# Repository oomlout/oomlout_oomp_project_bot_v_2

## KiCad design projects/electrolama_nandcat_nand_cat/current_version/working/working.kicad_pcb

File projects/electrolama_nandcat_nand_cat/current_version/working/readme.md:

# nandcat
 
## summary 
* id: electrolama_nandcat_nand_cat
* user: electrolama
* name: nandcat
* board: nand_cat
* repo: https://github.com/electrolama/nandcat
* src_file_repo_kicad_pcb: Revision A/nand-cat.kicad_pcb
* src_file_repo_kicad_pcb_link: https://github.com/electrolama/nandcat/tree/master/Revision A/nand-cat.kicad_pcb

* src_file_repo_sch: Revision A/nand-cat.sch
* src_file_repo_sch_link: https://github.com/electrolama/nandcat/tree/master/Revision A/nand-cat.sch
* full details link: https://github.com/oomlout/oomlout_oomp_project_bot_v_2/tree/main/projects/electrolama_nandcat_nand_cat/current_version/working  

## schematic  
  
[schematic (pdf)](working_schematic.pdf) 

## pcb  

[board (pdf)](working.pdf)  

## working_bom
| Id | Designator | Footprint | Quantity | Designation | Supplier and ref |  | None | 
| --- | --- | --- | --- | --- | --- | --- | --- | 
| 1 | J1 | PinHeader_2x03_P2.54mm_Vertical | 1 | Conn_02x03_Odd_Even |  |  | [''] | 
| 2 | SW2,SW1 | SW_SPST_B3S-1000 | 2 | SW_Push |  |  | [''] | 
| 3 | R2,R4,R1 | R_0603_1608Metric | 3 | 1K |  |  | [''] | 
| 4 | G*** | nand-cat | 1 | LOGO |  |  | [''] | 
| 5 | Q1,Q2 | SOT-23 | 2 | BC847B |  |  | [''] | 
| 6 | R5,R3 | R_0603_1608Metric | 2 | 100K |  |  | [''] | 
| 7 | D1 | LED_D3.0mm | 1 | LED |  |  | [''] | 

## bom_schematic
| Ref | Qnty | Value | Cmp name | Footprint | Description | Vendor | DNP | 
| --- | --- | --- | --- | --- | --- | --- | --- | 
| D1 | 1 | LED | LED | LED_THT:LED_D3.0mm | Light emitting diode |  |  | 
| J1 | 1 | Conn_02x03_Odd_Even | Conn_02x03_Odd_Even | Connector_PinHeader_2.54mm:PinHeader_2x03_P2.54mm_Vertical | Generic connector, double row, 02x03, odd/even pin numbering scheme (row 1 odd numbers, row 2 even numbers), script generated (kicad-library-utils/schlib/autogen/connector/) |  |  | 
| Q1, Q2 | 2 | BC847B | BC847 | Package_TO_SOT_SMD:SOT-23 | 0.1A Ic, 45V Vce, NPN Transistor, SOT-23 |  |  | 
| R1, R2, R4 | 3 | 1K | R | Resistor_SMD:R_0603_1608Metric | Resistor |  |  | 
| R3, R5 | 2 | 100K | R | Resistor_SMD:R_0603_1608Metric | Resistor |  |  | 
| SW1, SW2 | 2 | SW_Push | SW_Push | Button_Switch_SMD:SW_SPST_B3S-1000 | Push button switch, generic, two pins |  |  |

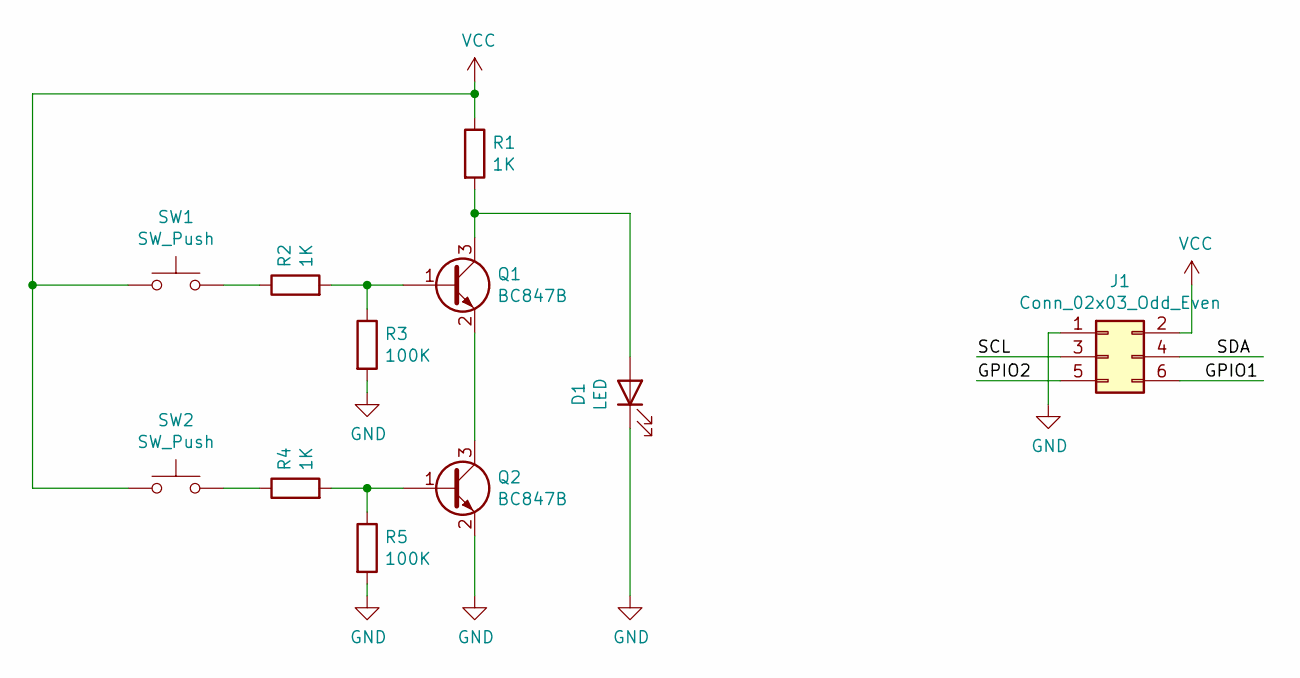
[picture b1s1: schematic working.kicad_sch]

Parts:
D1: LED; LED_D3.0mm
J1: Conn_02x03_Odd_Even; PinHeader_2x03_P2.54mm_Vertical
Q1, Q2: BC847B; SOT-23
R1, R2, R4: 1K; R_0603_1608Metric
R3, R5: 100K; R_0603_1608Metric
SW1, SW2: SW_Push; SW_SPST_B3S-1000

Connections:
/GPIO1: J1.6
/GPIO2: J1.5
/SCL: J1.3
/SDA: J1.4
GND: D1.1 (K), J1.1, Q2.2 (E), R3.2, R5.2
unnamed: D1.2 (A), Q1.3 (C), R1.2
unnamed: Q1.1 (B), R2.2, R3.1
unnamed: Q1.2 (E), Q2.3 (C)
unnamed: Q2.1 (B), R4.2, R5.1
unnamed: R2.1, SW1.2
unnamed: R4.1, SW2.2
VCC: J1.2, R1.1, SW1.1, SW2.1

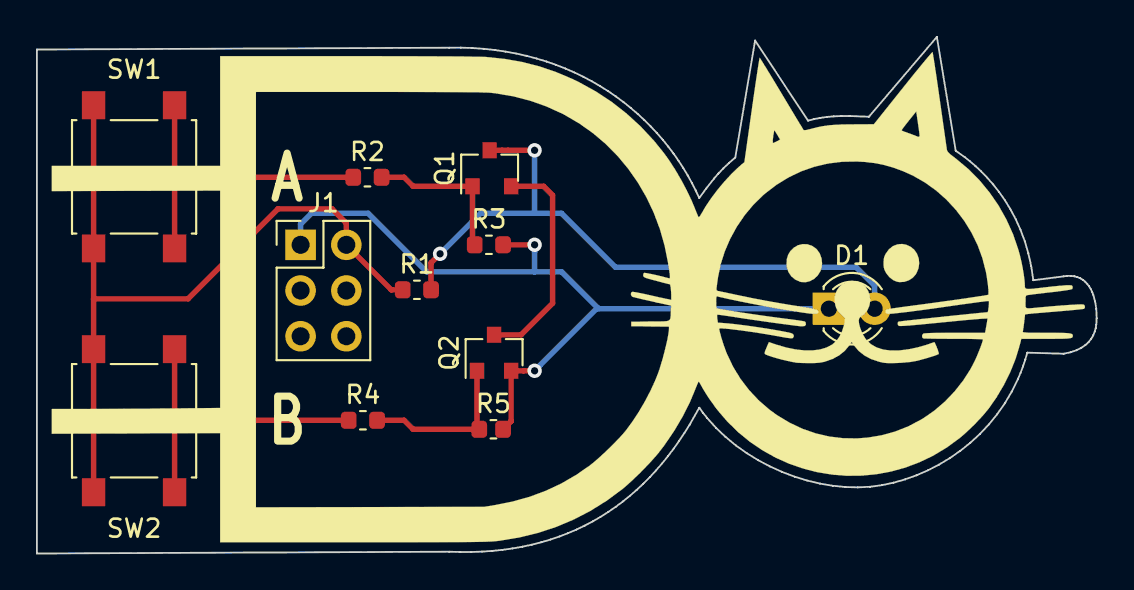
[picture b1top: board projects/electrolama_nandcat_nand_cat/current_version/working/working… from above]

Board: 2 copper layers, 58.9 x 28.7 mm, 11 parts (0 on the bottom side), 8 nets.

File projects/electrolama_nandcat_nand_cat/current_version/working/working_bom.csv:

"Id";"Designator";"Footprint";"Quantity";"Designation";"Supplier and ref";
1;"J1";"PinHeader_2x03_P2.54mm_Vertical";1;"Conn_02x03_Odd_Even";;;
2;"SW2,SW1";"SW_SPST_B3S-1000";2;"SW_Push";;;
3;"R2,R4,R1";"R_0603_1608Metric";3;"1K";;;
4;"G***";"nand-cat";1;"LOGO";;;
5;"Q1,Q2";"SOT-23";2;"BC847B";;;
6;"R5,R3";"R_0603_1608Metric";2;"100K";;;
7;"D1";"LED_D3.0mm";1;"LED";;;

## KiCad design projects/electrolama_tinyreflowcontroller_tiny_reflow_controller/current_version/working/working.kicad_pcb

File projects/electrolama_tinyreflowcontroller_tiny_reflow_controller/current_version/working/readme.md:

# tinyreflowcontroller
 
## summary 
* id: electrolama_tinyreflowcontroller_tiny_reflow_controller
* user: electrolama
* name: tinyreflowcontroller
* board: tiny_reflow_controller
* repo: https://github.com/electrolama/TinyReflowController
* src_file_repo_kicad_pcb: hardware/Revision A1/TINY-REFLOW-CONTROLLER.kicad_pcb
* src_file_repo_kicad_pcb_link: https://github.com/electrolama/TinyReflowController/tree/master/hardware/Revision A1/TINY-REFLOW-CONTROLLER.kicad_pcb
* src_file_repo_kicad_sch: hardware/Revision A1/TINY-REFLOW-CONTROLLER.kicad_sch
* src_file_repo_kicad_sch_link: https://github.com/electrolama/TinyReflowController/tree/master/hardware/Revision A1/TINY-REFLOW-CONTROLLER.kicad_sch

* src_file_repo_sch: 
* src_file_repo_sch_link: https://github.com/electrolama/TinyReflowController/tree/master/
* full details link: https://github.com/oomlout/oomlout_oomp_project_bot_v_2/tree/main/projects/electrolama_tinyreflowcontroller_tiny_reflow_controller/current_version/working  

## schematic  
  
[schematic (pdf)](working_schematic.pdf) 

## pcb  

[board (pdf)](working.pdf)  

## working_bom
| Id | Designator | Footprint | Quantity | Designation | Supplier and ref |  | None | 
| --- | --- | --- | --- | --- | --- | --- | --- | 
| 1 | U3 | TSSOP-14 | 1 | MAX31856 |  |  | [''] | 
| 2 | J2,J1,J5 | TB-1776275-2 | 3 | TERMINAL-BLOCK-1x2 |  |  | [''] | 
| 3 | Q2,Q1,Q3 | SOT-23 | 3 | 2N3904 |  |  | [''] | 
| 4 | R2,R3 | R_0603 | 2 | 100R |  |  | [''] | 
| 5 | R10,R9,R4,R5 | R_0603 | 4 | 10K |  |  | [''] | 
| 6 | R8,R12 | R_0603 | 2 | 53K6 |  |  | [''] | 
| 7 | R7 | R_0603 | 1 | 27K |  |  | [''] | 
| 8 | J3 | MICRO-USB | 1 | MICRO-USB |  |  | [''] | 
| 9 | LOGO1 | LOGO-ROCKET-SCREAM_Without_Text_XXXSmall | 1 | LOGO-ROCKET-SCREAM |  |  | [''] | 
| 10 | L1 | I_0603 | 1 | BLM18KG221SN1D |  |  | [''] | 
| 11 | SW2,SW1 | IT-1102W | 2 | IT-1109S |  |  | [''] | 
| 12 | LS1 | HYG9605B | 1 | HYG9605B |  |  | [''] | 
| 13 | C2,C1 | C_0603 | 2 | 10nF |  |  | [''] | 
| 14 | C9,C8,C7,C6,C4,C3,C13,C14,C18,C17,C11,C19 | C_0603 | 12 | 100nF |  |  | [''] | 
| 15 | C5,C12,C10 | C_0603 | 3 | 10uF 16V X5R |  |  | [''] | 
| 16 | D3 | SOD-323 | 1 | 1N4148WS |  |  | [''] | 
| 17 | R11,R1,R6 | R_0603 | 3 | 2K2 |  |  | [''] | 
| 18 | U1 | QFN-32_5x5mm_Pitch0.5mm | 1 | ATMEGA328P-MU |  |  | [''] | 
| 19 | U4 | MSOP-10 | 1 | CH340E |  |  | [''] | 
| 20 | F1 | MF-FSMF | 1 | FUSE |  |  | [''] | 
| 21 | L2 | I_0603 | 1 | LBMF1608T100K |  |  | [''] | 
| 22 | C16,C15 | C_0603 | 2 | 10pF |  |  | [''] | 
| 23 | D1 | LED_0603 | 1 | Red |  |  | [''] | 
| 24 | U2 | SOT-23 | 1 | MCP1700T-3302E-TT |  |  | [''] | 
| 25 | J9,J7,J8,J6 | PinHeader_1x02_P2.54mm_Vertical | 4 | 1x2 |  |  | [''] | 
| 26 | Y1 | Crystal_SMD_5032-2Pin_5.0x3.2mm | 1 | NX3225GD |  |  | [''] | 
| 27 | H1,H2,H4,H3 | MountingHole_2.2mm_M2 | 4 | M2 |  |  | [''] | 
| 28 | J10 | PinHeader_1x04_P2.54mm_Vertical | 1 | Conn_01x04 |  |  | [''] | 
| 29 | J4 | HDR_2x3_Pitch2.54mm | 1 | 2.54mm 2x3 |  |  | [''] | 
| 30 | LOGO2 | LOGO-KICAD_XSmall | 1 | LOGO-KICAD |  |  | [''] | 
| 31 | LOGO3 | LOGO-ROCKET-SCREAM_Vertical_Small | 1 | LOGO-ROCKET-SCREAM |  |  | [''] | 

## bom_schematic
| Ref | Qnty | Value | Cmp name | Footprint | Description | Vendor | DNP | 
| --- | --- | --- | --- | --- | --- | --- | --- | 
| C1, C2 | 2 | 10nF | CAPACITOR-CERAMIC-RocketScreamKiCadLib | RocketScreamKiCadLib:C_0603 |  |  |  | 
| C3, C4, C6, C7, C8, C9, C11, C13, C14, C17, C18, C19 | 12 | 100nF | CAPACITOR-CERAMIC-RocketScreamKiCadLib | RocketScreamKiCadLib:C_0603 |  |  |  | 
| C5, C10, C12 | 3 | 10uF 16V X5R | CAPACITOR-CERAMIC-RocketScreamKiCadLib | RocketScreamKiCadLib:C_0603 |  |  |  | 
| C15, C16 | 2 | 10pF | CAPACITOR-CERAMIC-RocketScreamKiCadLib | RocketScreamKiCadLib:C_0603 |  |  |  | 
| D1 | 1 | Red | LED-SINGLE-RocketScreamKiCadLib | RocketScreamKiCadLib:LED_0603 |  |  |  | 
| D3 | 1 | 1N4148WS | DIODE-RocketScreamKiCadLib | RocketScreamKiCadLib:SOD-323 |  |  |  | 
| F1 | 1 | FUSE | FUSE-RocketScreamKiCadLib | RocketScreamKiCadLib:MF-FSMF |  |  |  | 
| H1, H2, H3, H4 | 4 | M2 | MountingHole | MountingHole:MountingHole_2.2mm_M2 | Mounting Hole without connection |  |  | 
| J1, J2, J5 | 3 | TERMINAL-BLOCK-1x2 | TERMINAL-BLOCK-1x2-RocketScreamKiCadLib | RocketScreamKiCadLib:TB-1776275-2 |  |  |  | 
| J3 | 1 | MICRO-USB | MICRO-USB-RocketScreamKiCadLib | RocketScreamKiCadLib:MICRO-USB |  |  |  | 
| J4 | 1 | 2.54mm 2x3 | CONN-HDR-2x3-RocketScreamKiCadLib | RocketScreamKiCadLib:HDR_2x3_Pitch2.54mm |  |  |  | 
| J6, J7, J8, J9 | 4 | 1x2 | Conn_01x02 | Connector_PinHeader_2.54mm:PinHeader_1x02_P2.54mm_Vertical | Generic connector, single row, 01x02, script generated (kicad-library-utils/schlib/autogen/connector/) |  |  | 
| J10 | 1 | Conn_01x04 | Conn_01x04 | Connector_PinHeader_2.54mm:PinHeader_1x04_P2.54mm_Vertical | Generic connector, single row, 01x04, script generated (kicad-library-utils/schlib/autogen/connector/) |  |  | 
| L1 | 1 | BLM18KG221SN1D | INDUCTOR-RocketScreamKiCadLib | RocketScreamKiCadLib:I_0603 |  |  |  | 
| L2 | 1 | LBMF1608T100K | INDUCTOR-RocketScreamKiCadLib | RocketScreamKiCadLib:I_0603 |  |  |  | 
| LOGO1 | 1 | LOGO-ROCKET-SCREAM | LOGO-ROCKET-SCREAM-WITHOUT-TEXT-RocketScreamKiCadLib | RocketScreamKiCadLib:LOGO-ROCKET-SCREAM_Without_Text_XXXSmall |  |  |  | 
| LOGO2 | 1 | LOGO-KICAD | LOGO-KICAD-RocketScreamKiCadLib | RocketScreamKiCadLib:LOGO-KICAD_XSmall |  |  |  | 
| LOGO3 | 1 | LOGO-ROCKET-SCREAM | LOGO-ROCKET-SCREAM-WITHOUT-TEXT-RocketScreamKiCadLib | RocketScreamKiCadLib:LOGO-ROCKET-SCREAM_Vertical_Small |  |  |  | 
| LS1 | 1 | HYG9605B | BUZZER-RocketScreamKiCadLib | RocketScreamKiCadLib:HYG9605B |  |  |  | 
| Q1, Q2, Q3 | 3 | 2N3904 | BJT-NPN-RocketScreamKiCadLib | RocketScreamKiCadLib:SOT-23 |  |  |  | 
| R1, R6, R11 | 3 | 2K2 | RESISTOR-RocketScreamKiCadLib | RocketScreamKiCadLib:R_0603 |  |  |  | 
| R2, R3 | 2 | 100R | RESISTOR-RocketScreamKiCadLib | RocketScreamKiCadLib:R_0603 |  |  |  | 
| R4, R5, R9, R10 | 4 | 10K | RESISTOR-RocketScreamKiCadLib | RocketScreamKiCadLib:R_0603 |  |  |  | 
| R7 | 1 | 27K | RESISTOR-RocketScreamKiCadLib | RocketScreamKiCadLib:R_0603 |  |  |  | 
| R8, R12 | 2 | 53K6 | RESISTOR-RocketScreamKiCadLib | RocketScreamKiCadLib:R_0603 |  |  |  | 
| SW1, SW2 | 2 | IT-1109S | TACT-SWITCH_4Pins-RocketScreamKiCadLib | RocketScreamKiCadLib:IT-1102W |  |  |  | 
| U1 | 1 | ATMEGA328P-MU | ATMEGA328P-MU-RocketScreamKiCadLib | RocketScreamKiCadLib:QFN-32_5x5mm_Pitch0.5mm |  |  |  | 
| U2 | 1 | MCP1700T-3302E-TT | MCP1700T-XXX2E-TT-RocketScreamKiCadLib | RocketScreamKiCadLib:SOT-23 |  |  |  | 
| U3 | 1 | MAX31856 | MAX31856-RocketScreamKiCadLib | RocketScreamKiCadLib:TSSOP-14 |  |  |  | 
| U4 | 1 | CH340E | CH340E-RocketScreamKiCadLib | RocketScreamKiCadLib:MSOP-10 |  |  |  | 
| Y1 | 1 | NX3225GD | CRYSTAL-RocketScreamKiCadLib | Crystal:Crystal_SMD_5032-2Pin_5.0x3.2mm |  |  |  |

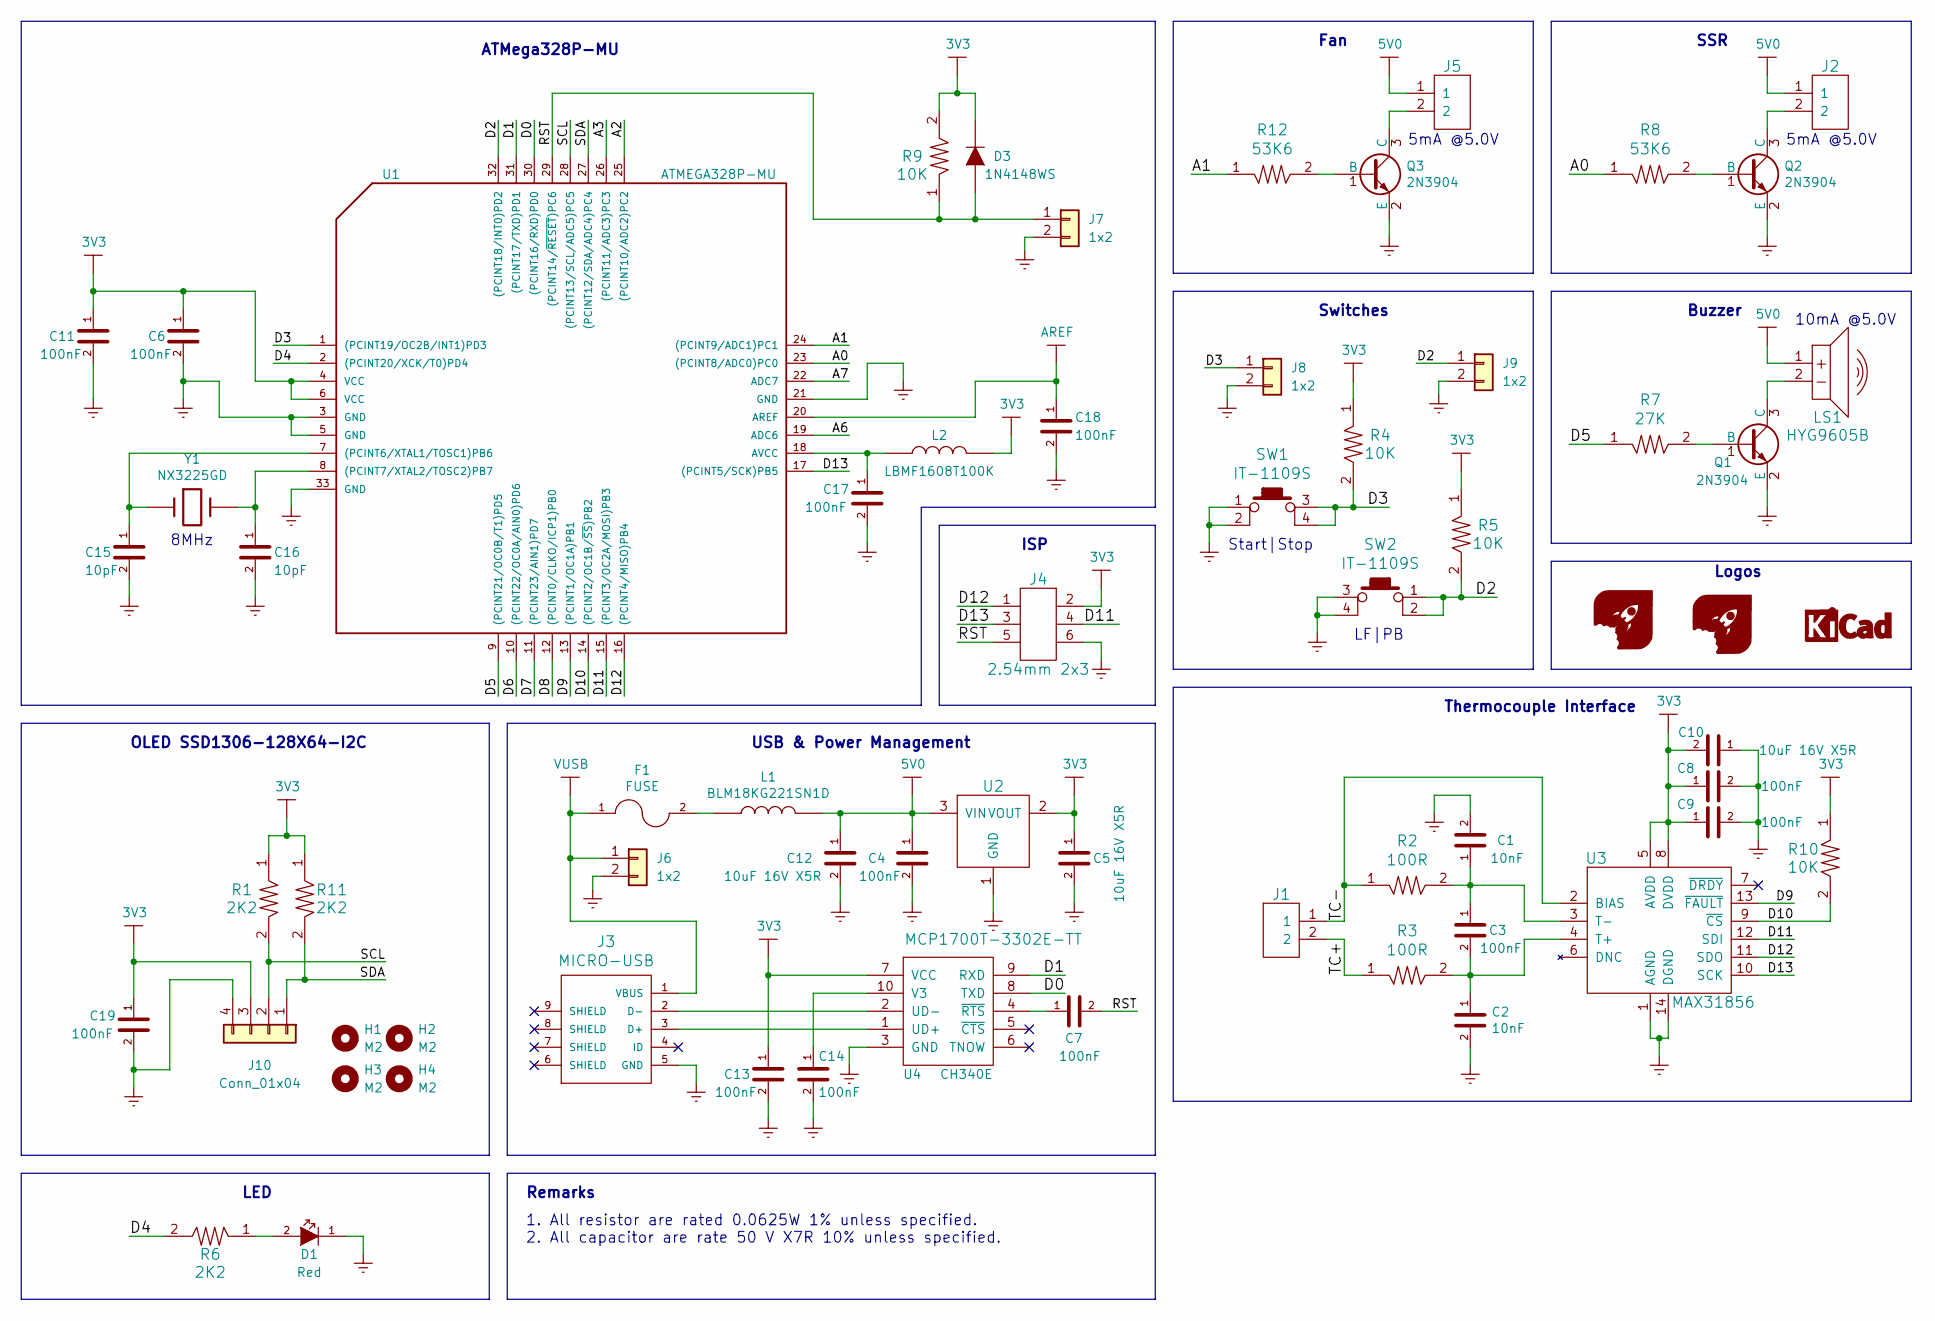
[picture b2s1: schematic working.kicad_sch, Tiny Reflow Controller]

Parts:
C1, C2: 10nF; C_0603
C3, C4, C6, C7, C8, C9, C11, C13, C14, C17, C18, C19: 100nF; C_0603
C5, C10, C12: 10uF 16V X5R; C_0603
C15, C16: 10pF; C_0603
D1: Red; LED_0603
D3: 1N4148WS; SOD-323
F1: FUSE; MF-FSMF
H1, H2, H3, H4: M2; MountingHole_2.2mm_M2
J1, J2, J5: TERMINAL-BLOCK-1x2; TB-1776275-2
J3: MICRO-USB
J4: 2.54mm 2x3; HDR_2x3_Pitch2.54mm
J6, J7, J8, J9: 1x2; PinHeader_1x02_P2.54mm_Vertical
J10: Conn_01x04; PinHeader_1x04_P2.54mm_Vertical
L1: BLM18KG221SN1D; I_0603
L2: LBMF1608T100K; I_0603
LOGO1: LOGO-ROCKET-SCREAM; LOGO-ROCKET-SCREAM_Without_Text_XXXSmall
LOGO2: LOGO-KICAD; LOGO-KICAD_XSmall
LOGO3: LOGO-ROCKET-SCREAM; LOGO-ROCKET-SCREAM_Vertical_Small
LS1: HYG9605B
Q1, Q2, Q3: 2N3904; SOT-23
R1, R6, R11: 2K2; R_0603
R2, R3: 100R; R_0603
R4, R5, R9, R10: 10K; R_0603
R7: 27K; R_0603
R8, R12: 53K6; R_0603
SW1, SW2: IT-1109S; IT-1102W
U1: ATMEGA328P-MU; QFN-32_5x5mm_Pitch0.5mm
U2: MCP1700T-3302E-TT; SOT-23
U3: MAX31856; TSSOP-14
U4: CH340E; MSOP-10
Y1: NX3225GD; Crystal_SMD_5032-2Pin_5.0x3.2mm

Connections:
3V3: C5.1, C6.1, C8.1, C9.1, C10.2, C11.1, C13.1, C19.1, D3.1 (K), J4.2, J10.3, L2.2, R1.1, R4.1, R5.1, R9.2, R10.1, R11.1, U1.4 (VCC), U1.6 (VCC), U2.2 (VOUT), U3.5 (AVDD), U3.8 (DVDD), U4.7 (VCC)
5V0: C4.1, C12.1, J2.1, J5.1, L1.2, LS1.1, U2.3 (VIN)
/A0: R8.1, U1.23 ((PCINT8/ADC0)PC0)
/A1: R12.1, U1.24 ((PCINT9/ADC1)PC1)
/A2: U1.25 ((PCINT10/ADC2)PC2)
/A3: U1.26 ((PCINT11/ADC3)PC3)
/A6: U1.19 (ADC6)
/A7: U1.22 (ADC7)
/D0: U1.30 ((PCINT16/RXD)PD0), U4.8 (TXD)
/D1: U1.31 ((PCINT17/TXD)PD1), U4.9 (RXD)
/D2: J9.1, R5.2, SW2.1, SW2.2, U1.32 ((PCINT18/INT0)PD2)
/D3: J8.1, R4.2, SW1.3, SW1.4, U1.1 ((PCINT19/OC2B/INT1)PD3)
/D4: R6.2, U1.2 ((PCINT20/XCK/T0)PD4)
/D5: R7.1, U1.9 ((PCINT21/OC0B/T1)PD5)
/D6: U1.10 ((PCINT22/OC0A/AIN0)PD6)
/D7: U1.11 ((PCINT23/AIN1)PD7)
/D8: U1.12 ((PCINT0/CLKO/ICP1)PB0)
/D9: U1.13 ((PCINT1/OC1A)PB1), U3.13 (~FAULT)
/D10: R10.2, U1.14 ((PCINT2/OC1B/~SS)PB2), U3.9 (~CS)
/D11: J4.4, U1.15 ((PCINT3/OC2A/MOSI)PB3), U3.12 (SDI)
/D12: J4.1, U1.16 ((PCINT4/MISO)PB4), U3.11 (SDO)
/D13: J4.3, U1.17 ((PCINT5/SCK)PB5), U3.10 (SCK)
/RST: C7.2, D3.2 (A), J4.5, J7.1, R9.1, U1.29 ((PCINT14/~RESET)PC6)
/SCL: J10.2, R1.2, U1.28 ((PCINT13/SCL/ADC5)PC5)
/SDA: J10.1, R11.2, U1.27 ((PCINT12/SDA/ADC4)PC4)
/TC+: J1.2, R3.1
/TC-: J1.1, R2.1, U3.2 (BIAS)
AREF: C18.1, U1.20 (AREF)
GND: C1.2, C2.2, C4.2, C5.2, C6.2, C8.2, C9.2, C10.1, C11.2, C12.2, C13.2, C14.2, C15.2, C16.2, C17.2, C18.2, C19.2, D1.1 (K), J3.5 (GND), J4.6, J6.2, J7.2, J8.2, J9.2, J10.4, Q1.2 (E), Q2.2 (E), Q3.2 (E), SW1.1, SW1.2, SW2.3, SW2.4, U1.3 (GND), U1.5 (GND), U1.21 (GND), U1.33 (GND), U2.1 (GND), U3.1 (AGND), U3.14 (DGND), U4.3 (GND)
unnamed: C1.1, C3.1, R2.2, U3.3 (T-)
unnamed: C2.1, C3.2, R3.2, U3.4 (T+)
unnamed: C7.1, U4.4 (~RTS)
unnamed: C14.1, U4.10 (V3)
unnamed: C15.1, U1.7 ((PCINT6/XTAL1/TOSC1)PB6), Y1.1
unnamed: C16.1, U1.8 ((PCINT7/XTAL2/TOSC2)PB7), Y1.2
unnamed: C17.1, L2.1, U1.18 (AVCC)
unnamed: D1.2 (A), R6.1
unnamed: F1.2, L1.1
unnamed: J2.2, Q2.3 (C)
unnamed: J3.2 (D-), U4.2 (UD-)
unnamed: J3.3 (D+), U4.1 (UD+)
unnamed: J5.2, Q3.3 (C)
unnamed: LS1.2, Q1.3 (C)
unnamed: Q1.1 (B), R7.2
unnamed: Q2.1 (B), R8.2
unnamed: Q3.1 (B), R12.2
VUSB: F1.1, J3.1 (VBUS), J6.1

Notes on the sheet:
Buzzer
5mA @5.0V
Fan
Logos
LF|PB
Remarks
10mA @5.0V
Switches
Start|Stop
1. All resistor are rated 0.0625W 1% unless specified. 2. All capacitor are rate 50 V X7R 10% unless specified.
ISP
Thermocouple Interface
8MHz
LED
ATMega328P-MU
USB & Power Management
SSR
OLED SSD1306-128X64-I2C

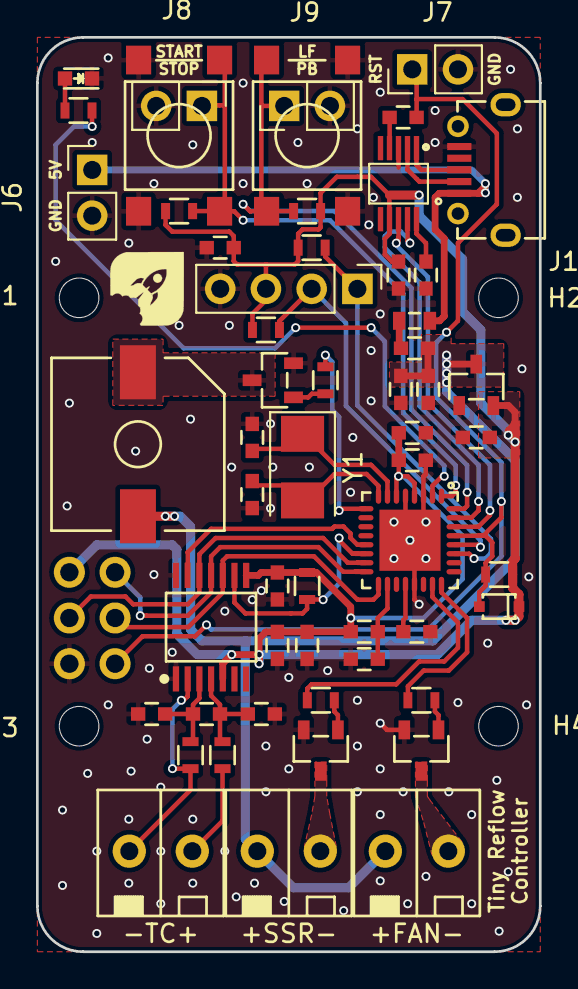
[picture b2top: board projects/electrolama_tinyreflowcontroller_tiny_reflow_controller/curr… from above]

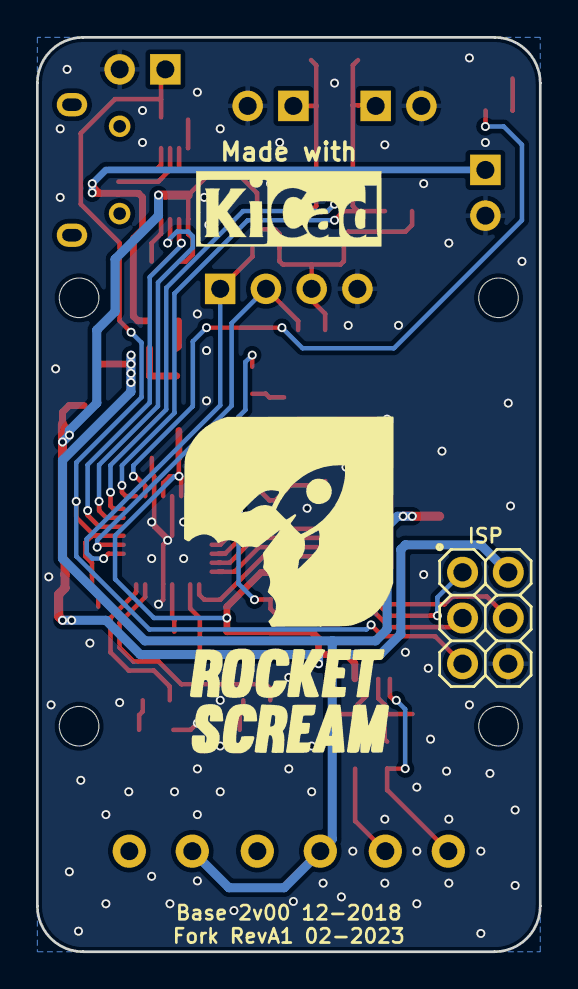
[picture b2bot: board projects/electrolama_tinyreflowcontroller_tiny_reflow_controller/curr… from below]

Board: 2 copper layers, 27.9 x 50.8 mm, 64 parts (3 on the bottom side), 40 nets.

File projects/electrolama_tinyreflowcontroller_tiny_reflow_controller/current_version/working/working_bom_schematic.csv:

"Source:","C:\gh\oomlout_oomp_project_bot_v_2\projects\electrolama_tinyreflowcontroller_tiny_reflow_controller\current_version\working\working.kicad_sch"
"Date:","11/09/2023 23:51:04"
"Tool:","Eeschema 7.0.6"
"Generator:","C:/Program Files/KiCad/7.0/bin/scripting/plugins/bom_csv_grouped_by_value_with_fp.py"
"Component Count:","64"
"Ref","Qnty","Value","Cmp name","Footprint","Description","Vendor","DNP"
"C1, C2","2","10nF","CAPACITOR-CERAMIC-RocketScreamKiCadLib","RocketScreamKiCadLib:C_0603","","",""
"C3, C4, C6, C7, C8, C9, C11, C13, C14, C17, C18, C19","12","100nF","CAPACITOR-CERAMIC-RocketScreamKiCadLib","RocketScreamKiCadLib:C_0603","","",""
"C5, C10, C12","3","10uF 16V X5R","CAPACITOR-CERAMIC-RocketScreamKiCadLib","RocketScreamKiCadLib:C_0603","","",""
"C15, C16","2","10pF","CAPACITOR-CERAMIC-RocketScreamKiCadLib","RocketScreamKiCadLib:C_0603","","",""
"D1","1","Red","LED-SINGLE-RocketScreamKiCadLib","RocketScreamKiCadLib:LED_0603","","",""
"D3","1","1N4148WS","DIODE-RocketScreamKiCadLib","RocketScreamKiCadLib:SOD-323","","",""
"F1","1","FUSE","FUSE-RocketScreamKiCadLib","RocketScreamKiCadLib:MF-FSMF","","",""
"H1, H2, H3, H4","4","M2","MountingHole","MountingHole:MountingHole_2.2mm_M2","Mounting Hole without connection","",""
"J1, J2, J5","3","TERMINAL-BLOCK-1x2","TERMINAL-BLOCK-1x2-RocketScreamKiCadLib","RocketScreamKiCadLib:TB-1776275-2","","",""
"J3","1","MICRO-USB","MICRO-USB-RocketScreamKiCadLib","RocketScreamKiCadLib:MICRO-USB","","",""
"J4","1","2.54mm 2x3","CONN-HDR-2x3-RocketScreamKiCadLib","RocketScreamKiCadLib:HDR_2x3_Pitch2.54mm","","",""
"J6, J7, J8, J9","4","1x2","Conn_01x02","Connector_PinHeader_2.54mm:PinHeader_1x02_P2.54mm_Vertical","Generic connector, single row, 01x02, script generated (kicad-library-utils/schlib/autogen/connector/)","",""
"J10","1","Conn_01x04","Conn_01x04","Connector_PinHeader_2.54mm:PinHeader_1x04_P2.54mm_Vertical","Generic connector, single row, 01x04, script generated (kicad-library-utils/schlib/autogen/connector/)","",""
"L1","1","BLM18KG221SN1D","INDUCTOR-RocketScreamKiCadLib","RocketScreamKiCadLib:I_0603","","",""
"L2","1","LBMF1608T100K","INDUCTOR-RocketScreamKiCadLib","RocketScreamKiCadLib:I_0603","","",""
"LOGO1","1","LOGO-ROCKET-SCREAM","LOGO-ROCKET-SCREAM-WITHOUT-TEXT-RocketScreamKiCadLib","RocketScreamKiCadLib:LOGO-ROCKET-SCREAM_Without_Text_XXXSmall","","",""
"LOGO2","1","LOGO-KICAD","LOGO-KICAD-RocketScreamKiCadLib","RocketScreamKiCadLib:LOGO-KICAD_XSmall","","",""
"LOGO3","1","LOGO-ROCKET-SCREAM","LOGO-ROCKET-SCREAM-WITHOUT-TEXT-RocketScreamKiCadLib","RocketScreamKiCadLib:LOGO-ROCKET-SCREAM_Vertical_Small","","",""
"LS1","1","HYG9605B","BUZZER-RocketScreamKiCadLib","RocketScreamKiCadLib:HYG9605B","","",""
"Q1, Q2, Q3","3","2N3904","BJT-NPN-RocketScreamKiCadLib","RocketScreamKiCadLib:SOT-23","","",""
"R1, R6, R11","3","2K2","RESISTOR-RocketScreamKiCadLib","RocketScreamKiCadLib:R_0603","","",""
"R2, R3","2","100R","RESISTOR-RocketScreamKiCadLib","RocketScreamKiCadLib:R_0603","","",""
"R4, R5, R9, R10","4","10K","RESISTOR-RocketScreamKiCadLib","RocketScreamKiCadLib:R_0603","","",""
"R7","1","27K","RESISTOR-RocketScreamKiCadLib","RocketScreamKiCadLib:R_0603","","",""
"R8, R12","2","53K6","RESISTOR-RocketScreamKiCadLib","RocketScreamKiCadLib:R_0603","","",""
"SW1, SW2","2","IT-1109S","TACT-SWITCH_4Pins-RocketScreamKiCadLib","RocketScreamKiCadLib:IT-1102W","","",""
"U1","1","ATMEGA328P-MU","ATMEGA328P-MU-RocketScreamKiCadLib","RocketScreamKiCadLib:QFN-32_5x5mm_Pitch0.5mm","","",""
"U2","1","MCP1700T-3302E-TT","MCP1700T-XXX2E-TT-RocketScreamKiCadLib","RocketScreamKiCadLib:SOT-23","","",""
"U3","1","MAX31856","MAX31856-RocketScreamKiCadLib","RocketScreamKiCadLib:TSSOP-14","","",""
"U4","1","CH340E","CH340E-RocketScreamKiCadLib","RocketScreamKiCadLib:MSOP-10","","",""
"Y1","1","NX3225GD","CRYSTAL-RocketScreamKiCadLib","Crystal:Crystal_SMD_5032-2Pin_5.0x3.2mm","","",""

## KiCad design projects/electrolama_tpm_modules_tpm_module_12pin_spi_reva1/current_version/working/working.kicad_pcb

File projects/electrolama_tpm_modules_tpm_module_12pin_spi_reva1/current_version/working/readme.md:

# tpm_modules
 
## summary 
* id: electrolama_tpm_modules_tpm_module_12pin_spi_reva1
* user: electrolama
* name: tpm_modules
* board: tpm_module_12pin_spi_reva1
* repo: https://github.com/electrolama/tpm-modules
* src_file_repo_kicad_pcb: tpm-module-12pin-spi/Revision A1/tpm-module-12pin-spi-RevA1.kicad_pcb
* src_file_repo_kicad_pcb_link: https://github.com/electrolama/tpm-modules/tree/main/tpm-module-12pin-spi/Revision A1/tpm-module-12pin-spi-RevA1.kicad_pcb
* src_file_repo_kicad_sch: tpm-module-12pin-spi/Revision A1/tpm-module-12pin-spi-RevA1.kicad_sch
* src_file_repo_kicad_sch_link: https://github.com/electrolama/tpm-modules/tree/main/tpm-module-12pin-spi/Revision A1/tpm-module-12pin-spi-RevA1.kicad_sch

* src_file_repo_sch: 
* src_file_repo_sch_link: https://github.com/electrolama/tpm-modules/tree/main/
* full details link: https://github.com/oomlout/oomlout_oomp_project_bot_v_2/tree/main/projects/electrolama_tpm_modules_tpm_module_12pin_spi_reva1/current_version/working  

## schematic  
  
[schematic (pdf)](working_schematic.pdf) 

## pcb  

[board (pdf)](working.pdf)  

## working_bom
| Id | Designator | Footprint | Quantity | Designation | Supplier and ref |  | None | 
| --- | --- | --- | --- | --- | --- | --- | --- | 
| 1 | C2,C3 | C_0402_1005Metric | 2 | 100n |  |  | [''] | 
| 2 | IC1 | QFN-32-1EP_5x5mm_P0.5mm_EP3.1x3.1mm | 1 | Infineon-SLB9670 |  |  | [''] | 
| 3 | C1 | C_0402_1005Metric | 1 | 4u7 |  |  | [''] | 
| 4 | R2,R1,R3 | R_0402_1005Metric | 3 | 10k |  |  | [''] | 
| 5 | J1 | PinSocket_2x06_P2.54mm_Horizontal | 1 | Conn_02x06_Odd_Even |  |  | [''] | 

## bom_schematic
| Ref | Qnty | Value | Cmp name | Footprint | Description | Vendor | DNP | 
| --- | --- | --- | --- | --- | --- | --- | --- | 
| C1 | 1 | 4u7 | C | Capacitor_SMD:C_0402_1005Metric | Unpolarized capacitor |  |  | 
| C2, C3 | 2 | 100n | C | Capacitor_SMD:C_0402_1005Metric | Unpolarized capacitor |  |  | 
| IC1 | 1 | Infineon-SLB9670 | Infineon-SLB9670 | Package_DFN_QFN:QFN-32-1EP_5x5mm_P0.5mm_EP3.1x3.1mm |  |  |  | 
| J1 | 1 | Conn_02x06_Odd_Even | Conn_02x06_Odd_Even | Connector_PinSocket_2.54mm:PinSocket_2x06_P2.54mm_Horizontal | Generic connector, double row, 02x06, odd/even pin numbering scheme (row 1 odd numbers, row 2 even numbers), script generated (kicad-library-utils/schlib/autogen/connector/) |  |  | 
| R1, R2, R3 | 3 | 10k | R | Resistor_SMD:R_0402_1005Metric | Resistor |  |  |

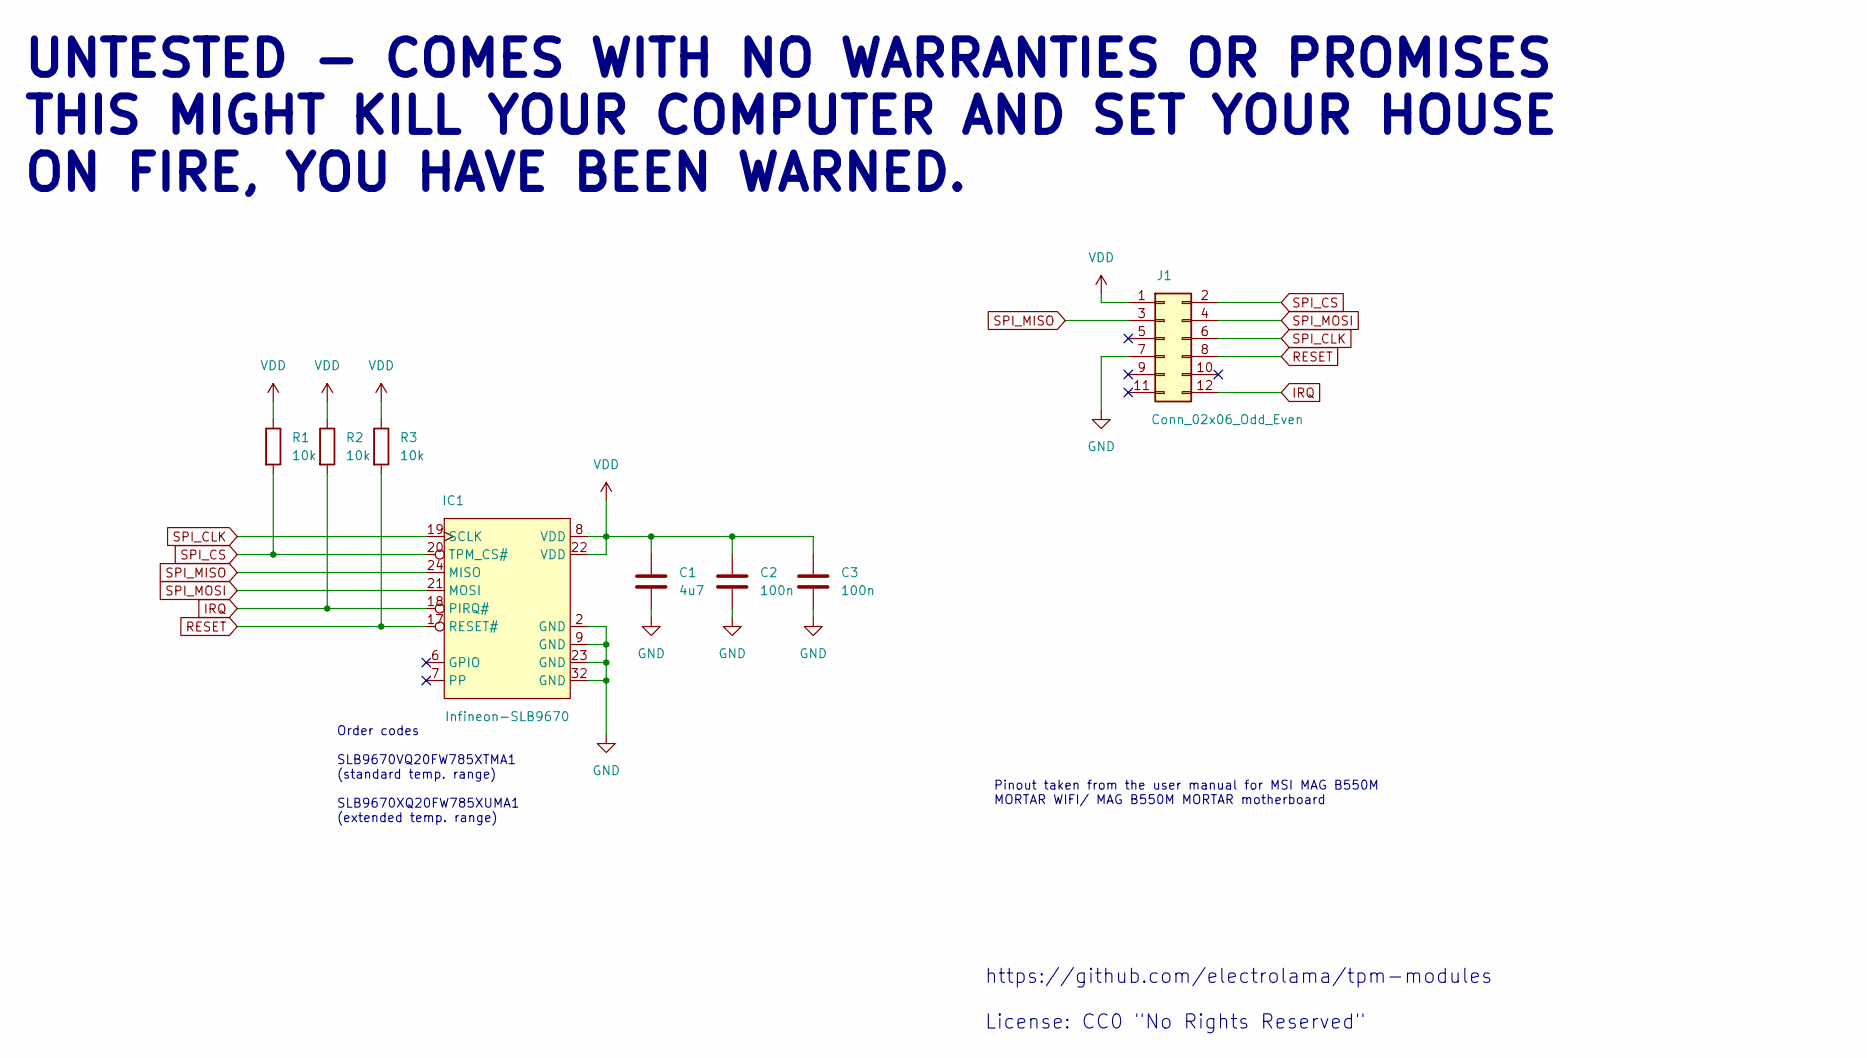
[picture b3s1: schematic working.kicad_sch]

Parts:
C1: 4u7; C_0402_1005Metric
C2, C3: 100n; C_0402_1005Metric
IC1: Infineon-SLB9670; QFN-32-1EP_5x5mm_P0.5mm_EP3.1x3.1mm
J1: Conn_02x06_Odd_Even; PinSocket_2x06_P2.54mm_Horizontal
R1, R2, R3: 10k; R_0402_1005Metric

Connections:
GND: C1.2, C2.2, C3.2, IC1.2 (GND), IC1.9 (GND), IC1.23 (GND), IC1.32 (GND), J1.7
IRQ: IC1.18 (PIRQ#), J1.12, R2.2
RESET: IC1.17 (RESET#), J1.8, R3.2
SPI_CLK: IC1.19 (SCLK), J1.6
SPI_CS: IC1.20 (TPM_CS#), J1.2, R1.2
SPI_MISO: IC1.24 (MISO), J1.3
SPI_MOSI: IC1.21 (MOSI), J1.4
VDD: C1.1, C2.1, C3.1, IC1.8 (VDD), IC1.22 (VDD), J1.1, R1.1, R2.1, R3.1

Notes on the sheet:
Order codes SLB9670VQ20FW785XTMA1 (standard temp. range) SLB9670XQ20FW785XUMA1 (extended temp. range)
Pinout taken from the user manual for MSI MAG B550M MORTAR WIFI/ MAG B550M MORTAR motherboard
UNTESTED - COMES WITH NO WARRANTIES OR PROMISES THIS MIGHT KILL YOUR COMPUTER AND SET YOUR HOUSE ON FIRE, YOU HAVE BEEN WARNED.
https://github.com/electrolama/tpm-modules License: CC0 "No Rights Reserved"

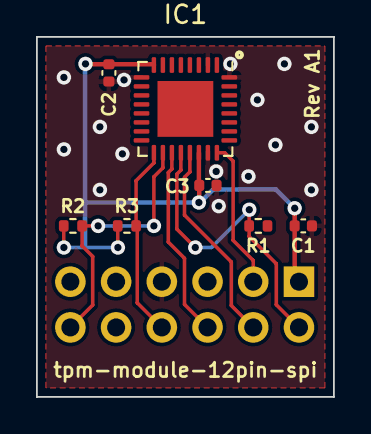
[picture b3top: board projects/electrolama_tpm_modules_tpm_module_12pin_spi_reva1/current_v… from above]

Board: 2 copper layers, 16.5 x 20.0 mm, 8 parts (1 on the bottom side), 8 nets.

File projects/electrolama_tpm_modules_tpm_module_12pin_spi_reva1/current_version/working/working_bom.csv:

"Id";"Designator";"Footprint";"Quantity";"Designation";"Supplier and ref";
1;"C2,C3";"C_0402_1005Metric";2;"100n";;;
2;"IC1";"QFN-32-1EP_5x5mm_P0.5mm_EP3.1x3.1mm";1;"Infineon-SLB9670";;;
3;"C1";"C_0402_1005Metric";1;"4u7";;;
4;"R2,R1,R3";"R_0402_1005Metric";3;"10k";;;
5;"J1";"PinSocket_2x06_P2.54mm_Horizontal";1;"Conn_02x06_Odd_Even";;;

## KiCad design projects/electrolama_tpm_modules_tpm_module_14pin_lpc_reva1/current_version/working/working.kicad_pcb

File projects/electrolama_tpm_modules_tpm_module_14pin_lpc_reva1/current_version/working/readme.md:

# tpm_modules
 
## summary 
* id: electrolama_tpm_modules_tpm_module_14pin_lpc_reva1
* user: electrolama
* name: tpm_modules
* board: tpm_module_14pin_lpc_reva1
* repo: https://github.com/electrolama/tpm-modules
* src_file_repo_kicad_pcb: tpm-module-14pin-lpc/Revision A1/tpm-module-14pin-lpc-RevA1.kicad_pcb
* src_file_repo_kicad_pcb_link: https://github.com/electrolama/tpm-modules/tree/main/tpm-module-14pin-lpc/Revision A1/tpm-module-14pin-lpc-RevA1.kicad_pcb
* src_file_repo_kicad_sch: tpm-module-14pin-lpc/Revision A1/tpm-module-14pin-lpc-RevA1.kicad_sch
* src_file_repo_kicad_sch_link: https://github.com/electrolama/tpm-modules/tree/main/tpm-module-14pin-lpc/Revision A1/tpm-module-14pin-lpc-RevA1.kicad_sch

* src_file_repo_sch: 
* src_file_repo_sch_link: https://github.com/electrolama/tpm-modules/tree/main/
* full details link: https://github.com/oomlout/oomlout_oomp_project_bot_v_2/tree/main/projects/electrolama_tpm_modules_tpm_module_14pin_lpc_reva1/current_version/working  

## schematic  
  
[schematic (pdf)](working_schematic.pdf) 

## pcb  

[board (pdf)](working.pdf)  

## working_bom
| Id | Designator | Footprint | Quantity | Designation | Supplier and ref |  | None | 
| --- | --- | --- | --- | --- | --- | --- | --- | 
| 1 | C5,C4,C2,C3,C6 | C_0402_1005Metric | 5 | 100n |  |  | [''] | 
| 2 | C1 | C_0402_1005Metric | 1 | 4u7 |  |  | [''] | 
| 3 | R2,R1 | R_0402_1005Metric | 2 | 10k |  |  | [''] | 
| 4 | IC1 | QFN-32-1EP_5x5mm_P0.5mm_EP3.1x3.1mm | 1 | Infineon-SLB9665 |  |  | [''] | 
| 5 | J1 | PinSocket_2x07_P2.54mm_Horizontal | 1 | Conn_02x07 |  |  | [''] | 

## bom_schematic
| Ref | Qnty | Value | Cmp name | Footprint | Description | Vendor | DNP | 
| --- | --- | --- | --- | --- | --- | --- | --- | 
| C1 | 1 | 4u7 | C | Capacitor_SMD:C_0402_1005Metric | Unpolarized capacitor |  |  | 
| C2, C3, C4, C5, C6 | 5 | 100n | C | Capacitor_SMD:C_0402_1005Metric | Unpolarized capacitor |  |  | 
| IC1 | 1 | Infineon-SLB9665 | Infineon-SLB9665 | Package_DFN_QFN:QFN-32-1EP_5x5mm_P0.5mm_EP3.1x3.1mm |  |  |  | 
| J1 | 1 | Conn_02x07 | Conn_02x07_Odd_Even | Connector_PinSocket_2.54mm:PinSocket_2x07_P2.54mm_Horizontal | Generic connector, double row, 02x07, odd/even pin numbering scheme (row 1 odd numbers, row 2 even numbers), script generated (kicad-library-utils/schlib/autogen/connector/) |  |  | 
| R1, R2 | 2 | 10k | R | Resistor_SMD:R_0402_1005Metric | Resistor |  |  |

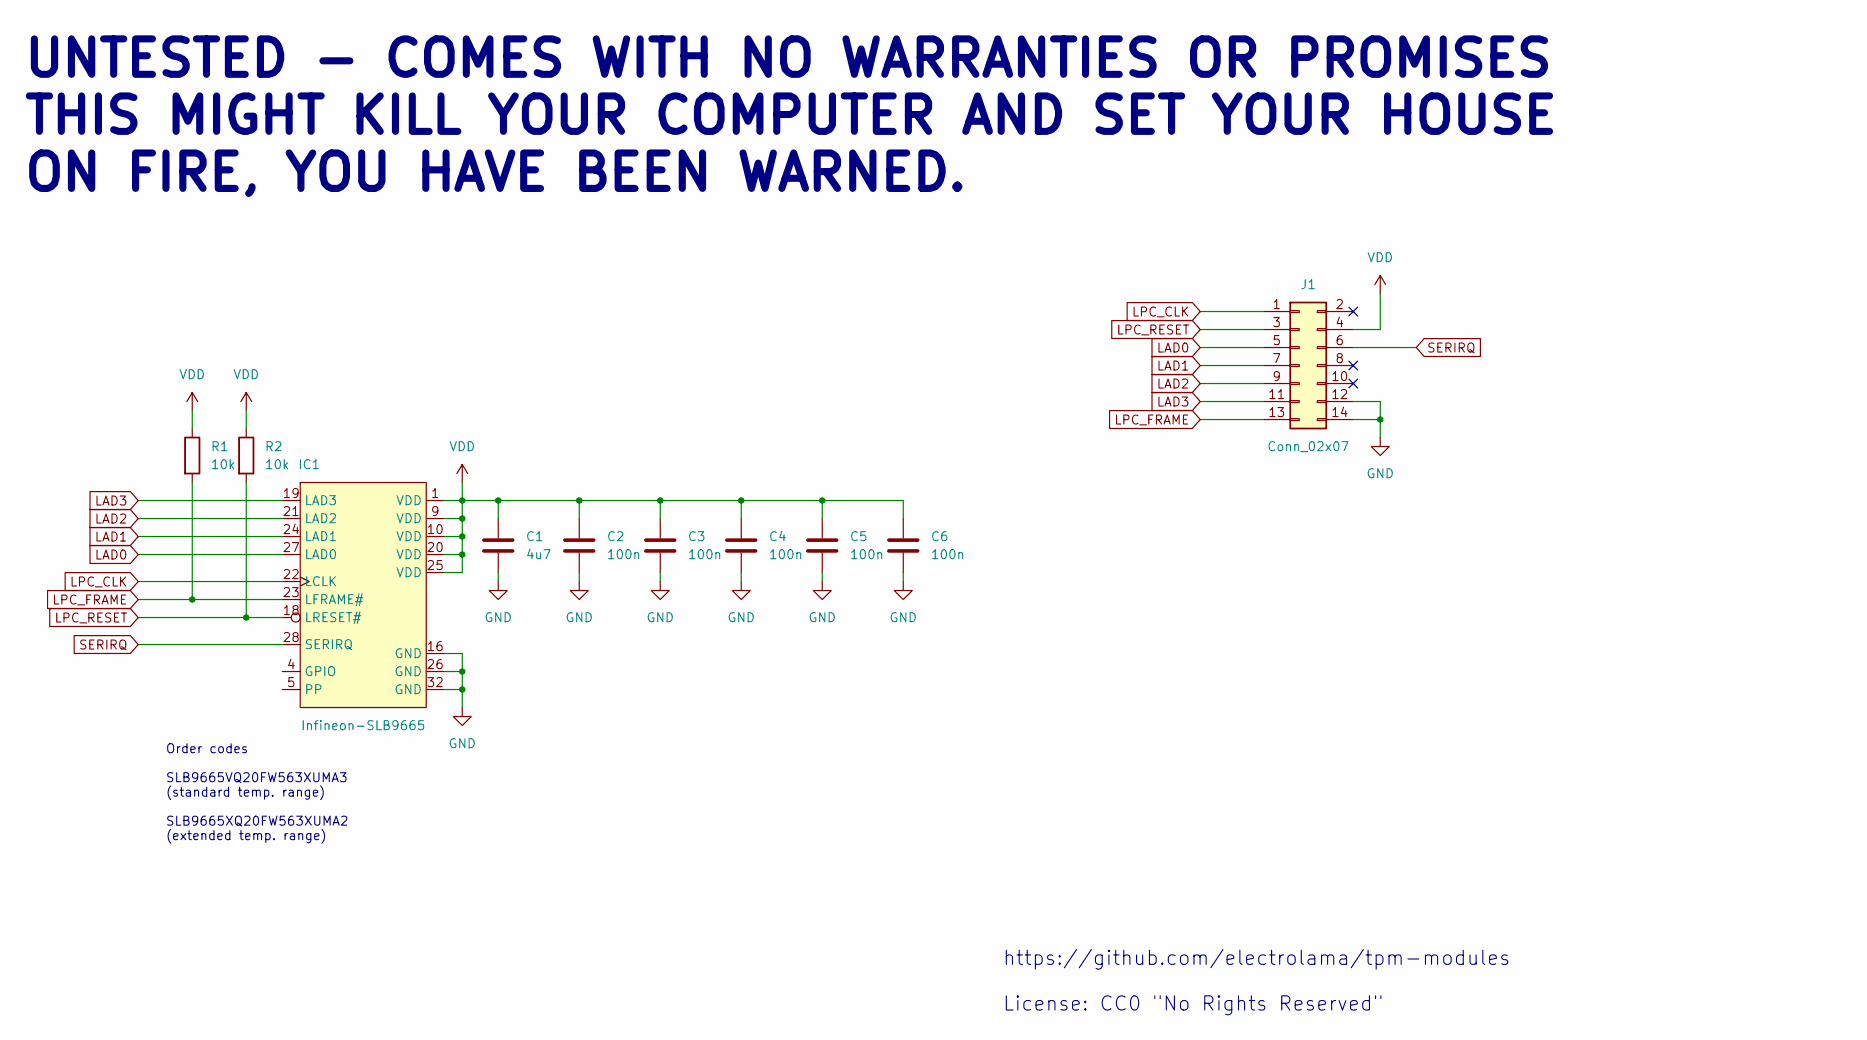
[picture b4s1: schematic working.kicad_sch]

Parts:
C1: 4u7; C_0402_1005Metric
C2, C3, C4, C5, C6: 100n; C_0402_1005Metric
IC1: Infineon-SLB9665; QFN-32-1EP_5x5mm_P0.5mm_EP3.1x3.1mm
J1: Conn_02x07; PinSocket_2x07_P2.54mm_Horizontal
R1, R2: 10k; R_0402_1005Metric

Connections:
GND: C1.2, C2.2, C3.2, C4.2, C5.2, C6.2, IC1.16 (GND), IC1.26 (GND), IC1.32 (GND), J1.12, J1.14
LAD0: IC1.27 (LAD0), J1.5
LAD1: IC1.24 (LAD1), J1.7
LAD2: IC1.21 (LAD2), J1.9
LAD3: IC1.19 (LAD3), J1.11
LPC_CLK: IC1.22 (LCLK), J1.1
LPC_FRAME: IC1.23 (LFRAME#), J1.13, R1.2
LPC_RESET: IC1.18 (LRESET#), J1.3, R2.2
SERIRQ: IC1.28 (SERIRQ), J1.6
VDD: C1.1, C2.1, C3.1, C4.1, C5.1, C6.1, IC1.1 (VDD), IC1.9 (VDD), IC1.10 (VDD), IC1.20 (VDD), IC1.25 (VDD), J1.4, R1.1, R2.1

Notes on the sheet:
Order codes SLB9665VQ20FW563XUMA3 (standard temp. range) SLB9665XQ20FW563XUMA2 (extended temp. range)
https://github.com/electrolama/tpm-modules License: CC0 "No Rights Reserved"
UNTESTED - COMES WITH NO WARRANTIES OR PROMISES THIS MIGHT KILL YOUR COMPUTER AND SET YOUR HOUSE ON FIRE, YOU HAVE BEEN WARNED.

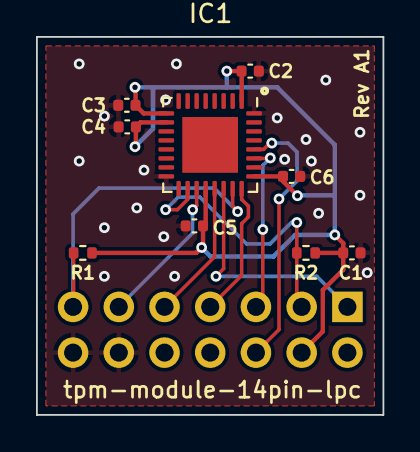
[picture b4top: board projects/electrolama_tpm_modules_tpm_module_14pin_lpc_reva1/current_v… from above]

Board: 2 copper layers, 19.2 x 21.0 mm, 10 parts (1 on the bottom side), 10 nets.

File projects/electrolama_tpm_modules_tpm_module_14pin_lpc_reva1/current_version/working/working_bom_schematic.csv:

"Source:","C:\gh\oomlout_oomp_project_bot_v_2\projects\electrolama_tpm_modules_tpm_module_14pin_lpc_reva1\current_version\working\working.kicad_sch"
"Date:","12/09/2023 00:04:53"
"Tool:","Eeschema 7.0.6"
"Generator:","C:/Program Files/KiCad/7.0/bin/scripting/plugins/bom_csv_grouped_by_value_with_fp.py"
"Component Count:","10"
"Ref","Qnty","Value","Cmp name","Footprint","Description","Vendor","DNP"
"C1","1","4u7","C","Capacitor_SMD:C_0402_1005Metric","Unpolarized capacitor","",""
"C2, C3, C4, C5, C6","5","100n","C","Capacitor_SMD:C_0402_1005Metric","Unpolarized capacitor","",""
"IC1","1","Infineon-SLB9665","Infineon-SLB9665","Package_DFN_QFN:QFN-32-1EP_5x5mm_P0.5mm_EP3.1x3.1mm","","",""
"J1","1","Conn_02x07","Conn_02x07_Odd_Even","Connector_PinSocket_2.54mm:PinSocket_2x07_P2.54mm_Horizontal","Generic connector, double row, 02x07, odd/even pin numbering scheme (row 1 odd numbers, row 2 even numbers), script generated (kicad-library-utils/schlib/autogen/connector/)","",""
"R1, R2","2","10k","R","Resistor_SMD:R_0402_1005Metric","Resistor","",""

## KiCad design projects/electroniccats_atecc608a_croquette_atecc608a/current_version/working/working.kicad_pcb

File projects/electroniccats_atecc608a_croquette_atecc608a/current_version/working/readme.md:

# atecc608a_croquette
 
## summary 
* id: electroniccats_atecc608a_croquette_atecc608a
* user: electroniccats
* name: atecc608a_croquette
* board: atecc608a
* repo: https://github.com/ElectronicCats/ATECC608A-Croquette
* src_file_repo_kicad_pcb: Kicad Files/ATECC608A.kicad_pcb
* src_file_repo_kicad_pcb_link: https://github.com/ElectronicCats/ATECC608A-Croquette/tree/master/Kicad Files/ATECC608A.kicad_pcb
* src_file_repo_kicad_sch: Kicad Files/ATECC608A.kicad_sch
* src_file_repo_kicad_sch_link: https://github.com/ElectronicCats/ATECC608A-Croquette/tree/master/Kicad Files/ATECC608A.kicad_sch

* src_file_repo_sch: Kicad Files/ATECC608A.sch
* src_file_repo_sch_link: https://github.com/ElectronicCats/ATECC608A-Croquette/tree/master/Kicad Files/ATECC608A.sch
* full details link: https://github.com/oomlout/oomlout_oomp_project_bot_v_2/tree/main/projects/electroniccats_atecc608a_croquette_atecc608a/current_version/working

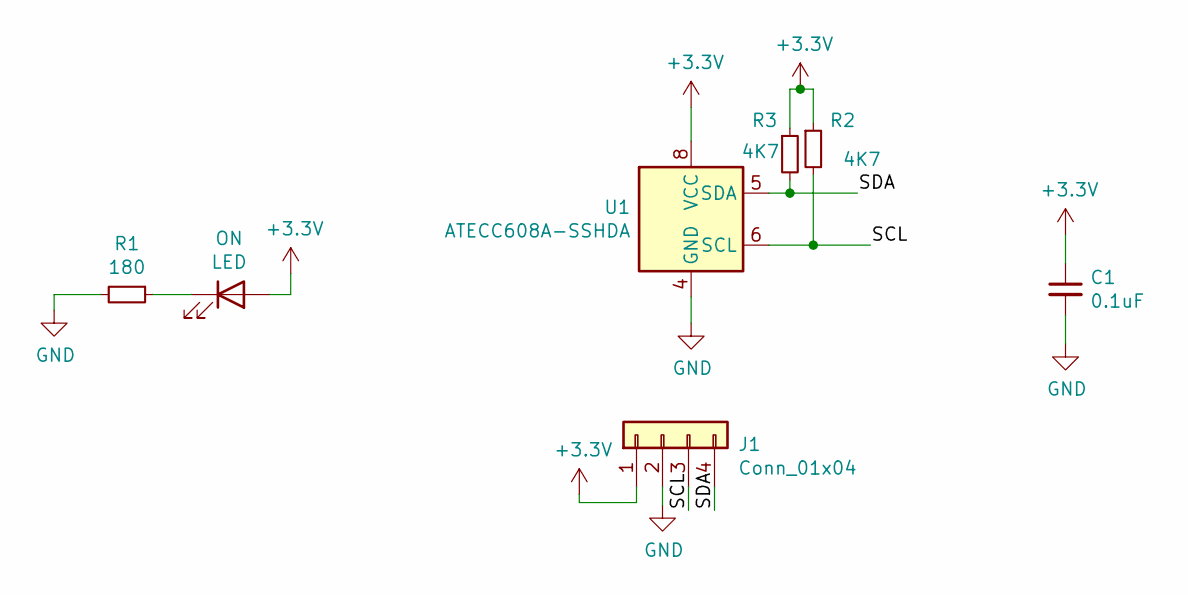
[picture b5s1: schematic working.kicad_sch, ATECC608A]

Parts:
C1: 0.1uF; C_0805_2012Metric_Pad1.15x1.40mm_HandSolder
J1: Conn_01x04; PinHeader_1x04_P2.54mm_Vertical
ON: LED; LED_0805_2012Metric_Pad1.15x1.40mm_HandSolder
R1: 180; R_0805_2012Metric_Pad1.15x1.40mm_HandSolder
R2, R3: 4K7; R_0805_2012Metric_Pad1.15x1.40mm_HandSolder
U1: ATECC608A-SSHDA; SOIC-8_3.9x4.9mm_P1.27mm

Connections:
+3V3: C1.1, J1.1, ON.2 (A), R2.1, R3.1, U1.8 (VCC)
/SCL: J1.3, R2.2, U1.6 (SCL)
/SDA: J1.4, R3.2, U1.5 (SDA)
GND: C1.2, J1.2, R1.2, U1.4 (GND)
unnamed: ON.1 (K), R1.1

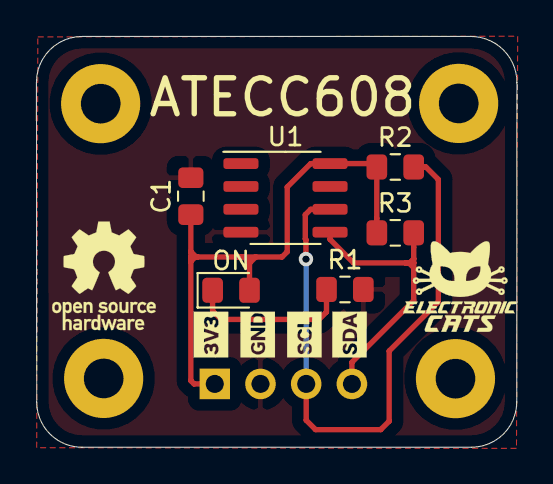
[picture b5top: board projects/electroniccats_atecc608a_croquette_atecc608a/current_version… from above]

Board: 2 copper layers, 26.7 x 22.8 mm, 7 parts (1 on the bottom side), 5 nets.
